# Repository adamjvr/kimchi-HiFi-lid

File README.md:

# Kimchi HiFi Lid — SGTL PCB

This directory contains the KiCad hardware files for the **SGTL5000-based audio PCB variant** of the Kimchi HiFi Lid project.

The board is an audio codec / interface PCB intended to mate with the main Kimchi hardware through high-density board-to-board connectors. It includes the audio codec, clocking, analog I/O connectors, EEPROM, local power filtering, and supporting passives required for the SGTL audio path.

## Design overview

Primary design intent:

- Provide a compact audio codec board for the Kimchi HiFi Lid assembly.
- Interface the audio codec and related signals to the parent system through two 60-pin Hirose board-to-board connectors.
- Break out analog audio through RCA and 3.5 mm audio connectors.
- Provide local clocking, EEPROM, level/interface support, and power filtering around the codec.

## Main functional blocks

- **Audio codec:** `U2` — `SGTL5000XNLA3`, NXP SGTL5000 stereo audio codec.
- **Clock source:** `X1` — `ASFL1-12.288MHZ-EC-T`, 12.288 MHz oscillator.
- **EEPROM:** `U1` — `24C32` / `M24C32-FMC6TG` I²C EEPROM.
- **Board-to-board connectors:** `J2`, `J3` — `DF40HC(3.5)-60DS` 60-pin connectors.
- **Analog audio I/O:**
  - `J1`, `J4` — `RCJ-2123` RCA jacks.
  - `J5` — `54-00176` 3.5 mm audio jack.
  - `MIC_IN` and `MIC_BIAS` nets for microphone input support.
- **Logic support:** `U3` — `SN74LV1T34DBVRG4` single-bit buffer / level interface.
- **Power rails and filtering:** `VDD_5V`, `VDD_3V3`, `VDD_1V8`, ferrite beads, bulk capacitance, and local bypassing.

## Directory contents

| Path | Purpose |
|---|---|
| `kimchi_ulid.sch` | Main KiCad / Eeschema schematic. |
| `kimchi_ulid.sch-bak` | Backup copy of the schematic. |
| `kimchi_ulid.lib` | Local symbol library. |
| `kimchi_ulid-cache.lib` | Cached schematic symbols. |
| `kimchi_ulid.dcm` | KiCad symbol documentation metadata. |
| `kimchi_ulid.csv` | BOM / component export. See warning below before ordering. |
| `kimchi_ulid.xml` | KiCad-generated netlist / BOM source export. |
| `kimchi_ulid.pretty/` | Local KiCad footprints and related 3D assets. |
| `gerber/` | Exported manufacturing files. |
| `sym-lib-table` | KiCad symbol library table. |
| `fp-lib-table` | KiCad footprint library table. |

## KiCad version notes

This project uses the older KiCad / Eeschema file format, with the schematic stored as `kimchi_ulid.sch`.

For editing in a newer KiCad release:

1. Open the project/schematic in KiCad.
2. Let KiCad convert legacy schematic/library data if prompted.
3. Save the converted project on a new branch before overwriting the original files.
4. Re-run ERC, DRC, BOM export, and Gerber generation after conversion.

## Fabrication notes

The `gerber/` directory contains exported fabrication data, including copper, solder mask, silkscreen, fabrication, and edge-cut files.

Before sending this board out for manufacture, regenerate the manufacturing package from the current KiCad project and verify:

- Board outline and mounting holes.
- Layer stackup, especially the inner copper layers.
- DF40 connector orientation, stack height, and mating-board alignment.
- RCA and 3.5 mm jack mechanical clearance.
- Power rail assignments from the parent board.
- Audio routing, grounding, and codec analog supply filtering.
- I²C / digital audio signal mapping to the parent processor.

## Important BOM warning

The schematic in this SGTL folder uses `SGTL5000XNLA3` for `U2`, but the checked-in `kimchi_ulid.csv` may be stale and may still list `U2` as `WM8750CJLGEFL` from an earlier codec revision.

Do **not** order directly from the CSV without regenerating the BOM from the current schematic.

Recommended release process:

1. Open the schematic in KiCad.
2. Confirm `U2` is the intended SGTL5000 part.
3. Regenerate the BOM / CSV from the active schematic.
4. Compare the regenerated BOM against the committed `kimchi_ulid.csv`.
5. Update the CSV before fabrication or assembly.

## Bring-up checklist

Suggested first-power and validation flow:

- Inspect the board for solder bridges, especially around the codec QFN and DF40 connectors.
- Verify no shorts on `VDD_5V`, `VDD_3V3`, `VDD_1V8`, and ground before power-up.
- Power the board from a current-limited bench supply or through the intended parent board with current monitoring.
- Confirm local rails are present and stable.
- Confirm the 12.288 MHz oscillator output.
- Verify I²C communication with the codec and EEPROM.
- Confirm codec reset / enable behavior if controlled by the parent system.
- Test analog output at low level first, then validate full-scale playback.
- Test microphone input and bias only after confirming the audio codec is enumerating/configuring correctly.

## Status

Hardware design files and generated manufacturing outputs are present, but this directory should be treated as an engineering design package rather than a guaranteed production release. Regenerate and review all release outputs before ordering boards or parts.

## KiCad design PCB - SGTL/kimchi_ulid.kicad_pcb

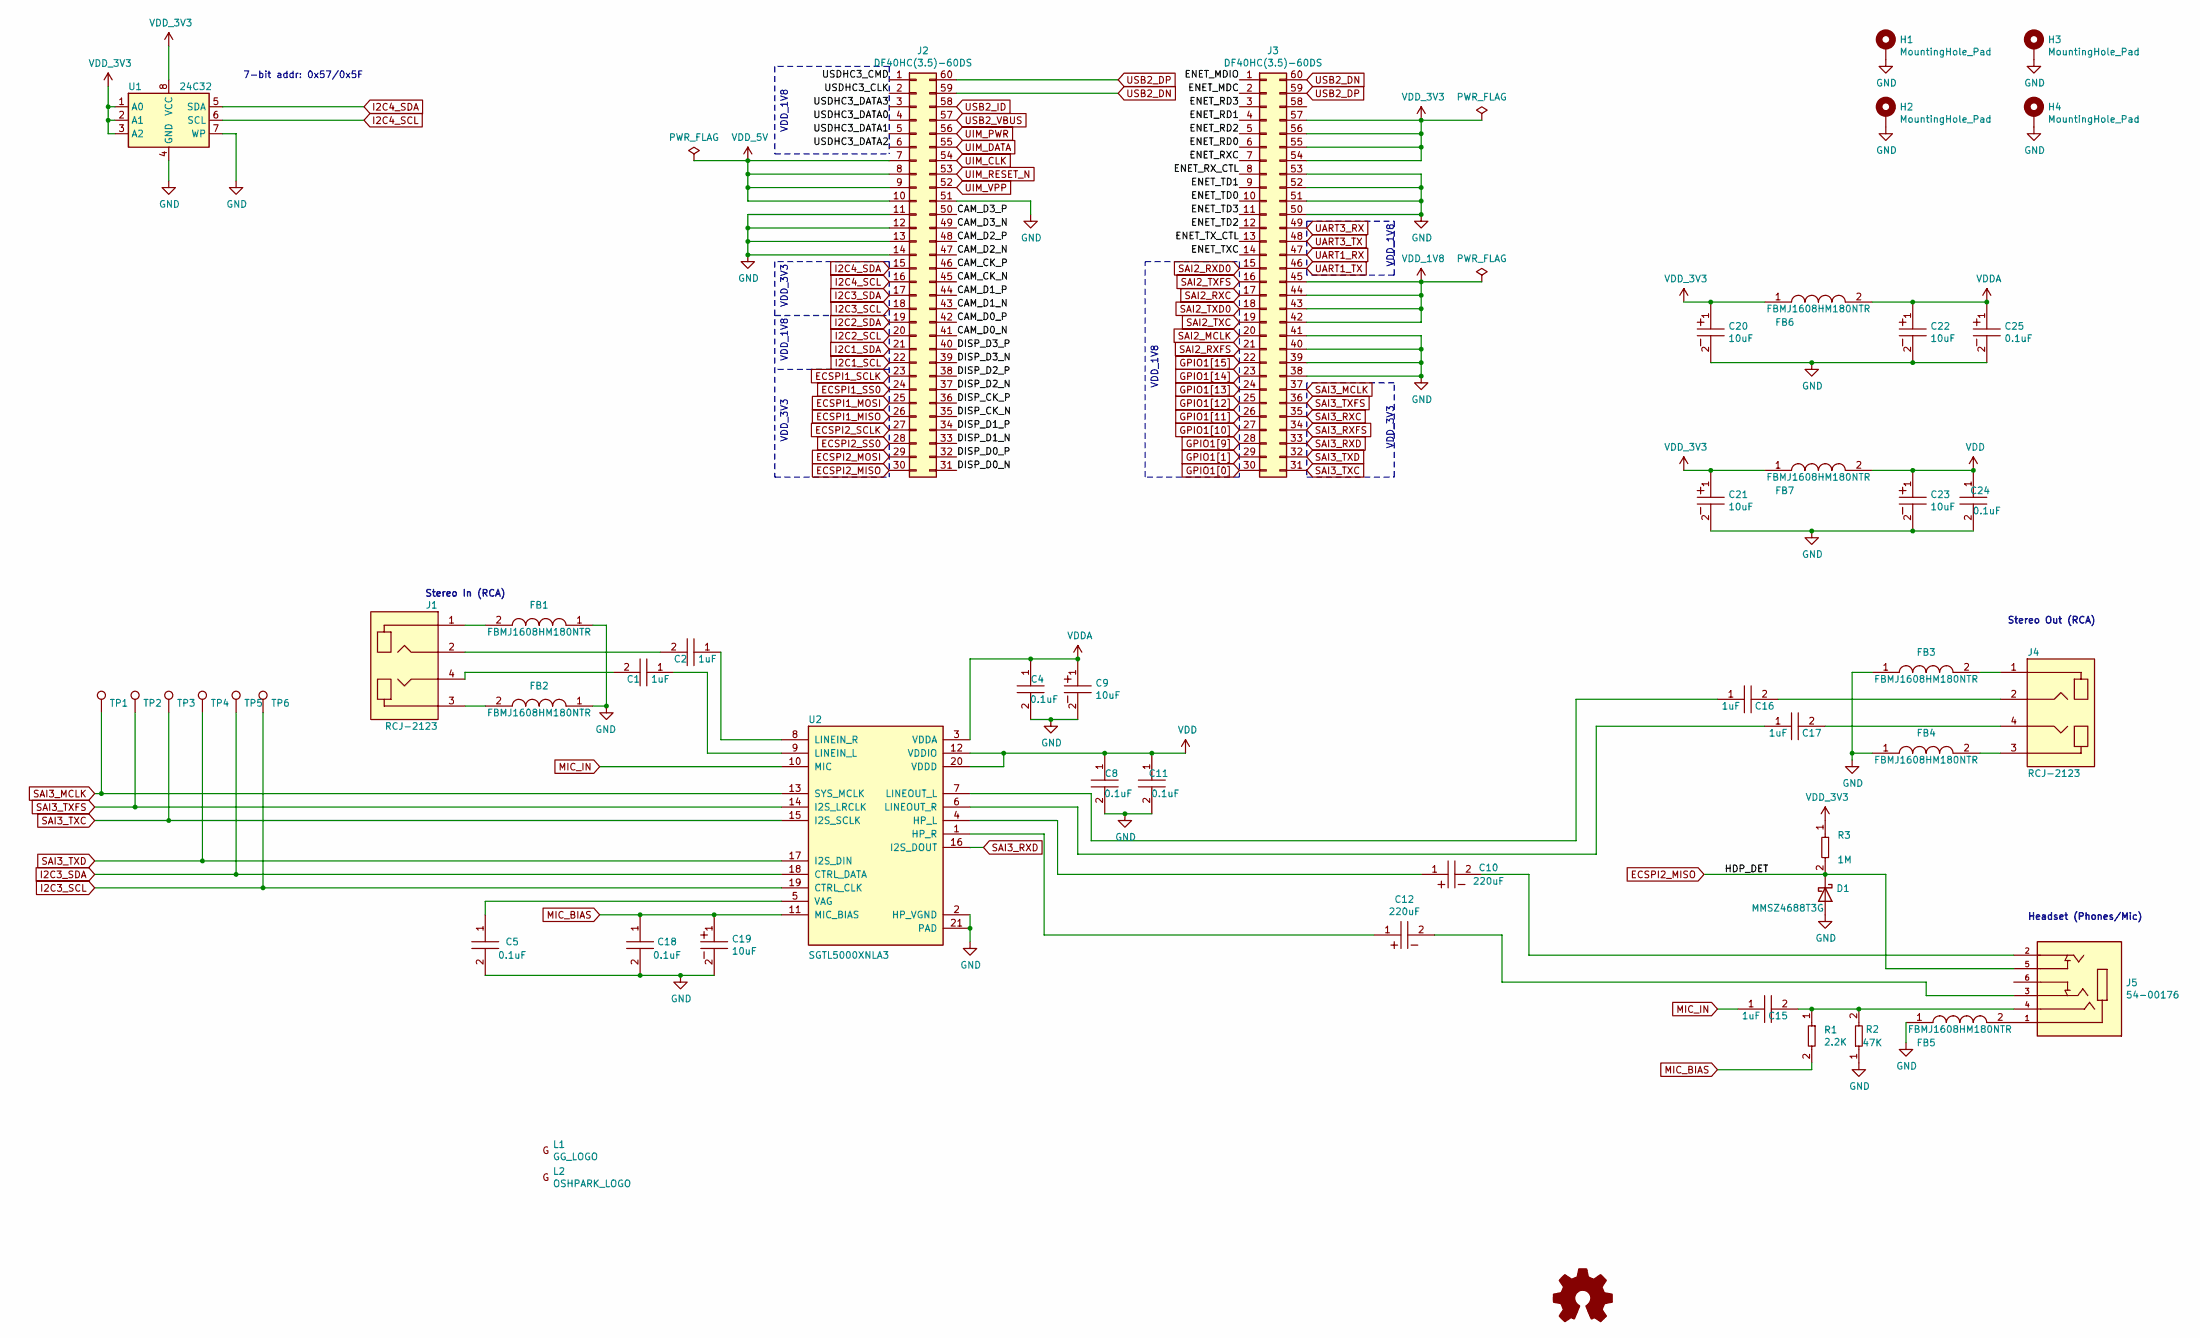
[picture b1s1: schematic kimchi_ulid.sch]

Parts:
C1, C2, C15, C16, C17: T491A105K010AT; C1206; Tolerance 10%; Voltage 10V; MFR# T491A105K010AT
C4, C5, C8, C11, C18, C24: C0402C104K9PACTU; C0402; Tolerance 10%; Voltage 6.3V; MFR# C0402C104K9PACTU
C9, C19, C20, C21, C22, C23: T494A106M006AT; Tolerance 20%; Voltage 6.3V; MFR# T494A106M006AT
C10, C12: T491D227M010AT; Tolerance 10%; Voltage 10VDC; MFR# T491D227M010AT
C25: UZP1H0R1MCL1GB; Tolerance 20%; Voltage 50V; MFR# UZP1H0R1MCL1GB
D1: MMSZ4688T3G
FB1, FB2, FB3, FB4, FB5, FB6, FB7: FBMJ1608HM180NTR; R0603; Tolerance *; Voltage *; MFR# FBMJ1608HM180NTR
H1, H2, H3, H4: MountingHole_Pad; MountingHole_3mm_Pad
J1, J4: RCJ-2123; Tolerance *; Voltage 24VDC; MFR# RCJ-2123
J2, J3: DF40HC(3.5)-60DS
J5: 54-00176; Tolerance *; Voltage *; MFR# 54-00176
L1: GG_LOGO; groupgets_logo
L2: OSHPARK_LOGO; oshpark_logo
LOGO1: Logo_Open_Hardware_Small; OSHW-Logo_5.7x6mm_SilkScreen
R1: RC0402JR-072K2L; R0402; Tolerance 1%; Voltage *; MFR# RC0402JR-072K2L
R2: RC0603FR-0747KL; R0603; Tolerance 1%; Voltage *; MFR# RC0603FR-0747KL
R3: AC0402FR-071ML; R0402; Tolerance 1%; Voltage *; MFR# AC0402FR-071ML
TP1, TP2, TP3, TP4, TP5, TP6: TestPoint; TestPoint_Pad_D1.0mm
U1: 24C32; DFN-8-1EP_3x2mm_P0.5mm_EP1.36x1.46mm; Part M24C32-FMC6TG
U2: SGTL5000XNLA3; QFN40P300X300X60-21N; Tolerance *; Voltage 3.3V; MFR# SGTL5000XNLA3

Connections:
/CAM_CK_N: J2.45
/CAM_CK_P: J2.46
/CAM_D0_N: J2.41
/CAM_D0_P: J2.42
/CAM_D1_N: J2.43
/CAM_D1_P: J2.44
/CAM_D2_N: J2.47
/CAM_D2_P: J2.48
/CAM_D3_N: J2.49
/CAM_D3_P: J2.50
/DISP_CK_N: J2.35
/DISP_CK_P: J2.36
/DISP_D0_N: J2.31
/DISP_D0_P: J2.32
/DISP_D1_N: J2.33
/DISP_D1_P: J2.34
/DISP_D2_N: J2.37
/DISP_D2_P: J2.38
/DISP_D3_N: J2.39
/DISP_D3_P: J2.40
/ENET_MDC: J3.2
/ENET_MDIO: J3.1
/ENET_RD0: J3.6
/ENET_RD1: J3.4
/ENET_RD2: J3.5
/ENET_RD3: J3.3
/ENET_RXC: J3.7
/ENET_RX_CTL: J3.8
/ENET_TD0: J3.10
/ENET_TD1: J3.9
/ENET_TD2: J3.12
/ENET_TD3: J3.11
/ENET_TXC: J3.14
/ENET_TX_CTL: J3.13
/USDHC3_CLK: J2.2
/USDHC3_CMD: J2.1
/USDHC3_DATA0: J2.4
/USDHC3_DATA1: J2.5
/USDHC3_DATA2: J2.6
/USDHC3_DATA3: J2.3
ECSPI1_MISO: J2.26
ECSPI1_MOSI: J2.25
ECSPI1_SCLK: J2.23
ECSPI1_SS0: J2.24
ECSPI2_MISO: D1.1 (K), J2.30, J5.5, R3.2
ECSPI2_MOSI: J2.29
ECSPI2_SCLK: J2.27
ECSPI2_SS0: J2.28
GND: C4.2, C5.2, C8.2, C9.2, C11.2, C18.2, C19.2, C20.2, C21.2, C22.2, C23.2, C24.2, C25.2, D1.2 (A), FB1.1, FB2.1, FB3.1, FB4.1, FB5.1, H1.1, H2.1, H3.1, H4.1, J2.11, J2.12, J2.13, J2.14, J2.51, J3.38, J3.39, J3.40, J3.41, J3.50, J3.51, J3.52, J3.53, R2.1, U1.4 (GND), U1.7 (WP), U2.2 (HP_VGND), U2.21 (PAD)
GPIO1[0]: J3.30
GPIO1[1]: J3.29
GPIO1[9]: J3.28
GPIO1[10]: J3.27
GPIO1[11]: J3.26
GPIO1[12]: J3.25
GPIO1[13]: J3.24
GPIO1[14]: J3.23
GPIO1[15]: J3.22
I2C1_SCL: J2.22
I2C1_SDA: J2.21
I2C2_SCL: J2.20
I2C2_SDA: J2.19
I2C3_SCL: J2.18, TP6.1, U2.19 (CTRL_CLK)
I2C3_SDA: J2.17, TP5.1, U2.18 (CTRL_DATA)
I2C4_SCL: J2.16, U1.6 (SCL)
I2C4_SDA: J2.15, U1.5 (SDA)
MIC_BIAS: C18.1, C19.1, R1.2, U2.11 (MIC_BIAS)
MIC_IN: C15.1, U2.10 (MIC)
unnamed: C1.1, U2.9 (LINEIN_L)
unnamed: C1.2, J1.4
unnamed: C2.1, U2.8 (LINEIN_R)
unnamed: C2.2, J1.2
unnamed: C5.1, U2.5 (VAG)
unnamed: C10.1, U2.4 (HP_L)
unnamed: C10.2, J5.2
unnamed: C12.1, U2.1 (HP_R)
unnamed: C12.2, J5.3
unnamed: C15.2, J5.4, R1.1, R2.2
unnamed: C16.2, J4.2
unnamed: C17.2, J4.4
unnamed: FB1.2, J1.1
unnamed: FB2.2, J1.3
unnamed: FB3.2, J4.1
unnamed: FB4.2, J4.3
unnamed: FB5.2, J5.1
SAI2_MCLK: J3.20
SAI2_RXC: J3.17
SAI2_RXD0: J3.15
SAI2_RXFS: J3.21
SAI2_TXC: J3.19
SAI2_TXD0: J3.18
SAI2_TXFS: J3.16
SAI3_MCLK: J3.37, TP1.1, U2.13 (SYS_MCLK)
SAI3_RXC: J3.35
SAI3_RXD: J3.33, U2.16 (I2S_DOUT)
SAI3_RXFS: J3.34
SAI3_TXC: J3.31, TP3.1, U2.15 (I2S_SCLK)
SAI3_TXD: J3.32, TP4.1, U2.17 (I2S_DIN)
SAI3_TXFS: J3.36, TP2.1, U2.14 (I2S_LRCLK)
UART1_RX: J3.47
UART1_TX: J3.46
UART3_RX: J3.49
UART3_TX: J3.48
UIM_CLK: J2.54
UIM_DATA: J2.55
UIM_PWR: J2.56
UIM_RESET_N: J2.53
UIM_VPP: J2.52
USB2_DN: J2.59, J3.60
USB2_DP: J2.60, J3.59
USB2_ID: J2.58
USB2_VBUS: J2.57
VDD: C8.1, C11.1, C23.1, C24.1, FB7.2, U2.12 (VDDIO), U2.20 (VDDD)
VDDA: C4.1, C9.1, C22.1, C25.1, FB6.2, U2.3 (VDDA)
VDD_1V8: J3.42, J3.43, J3.44, J3.45
VDD_3V3: C20.1, C21.1, FB6.1, FB7.1, J3.54, J3.55, J3.56, J3.57, R3.1, U1.1 (A0), U1.2 (A1), U1.3 (A2), U1.8 (VCC)
VDD_5V: J2.7, J2.8, J2.9, J2.10

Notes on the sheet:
7-bit addr: 0x57/0x5F
VDD_1V8
VDD_3V3
Headset (Phones/Mic)
Stereo Out (RCA)
Stereo In (RCA)

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
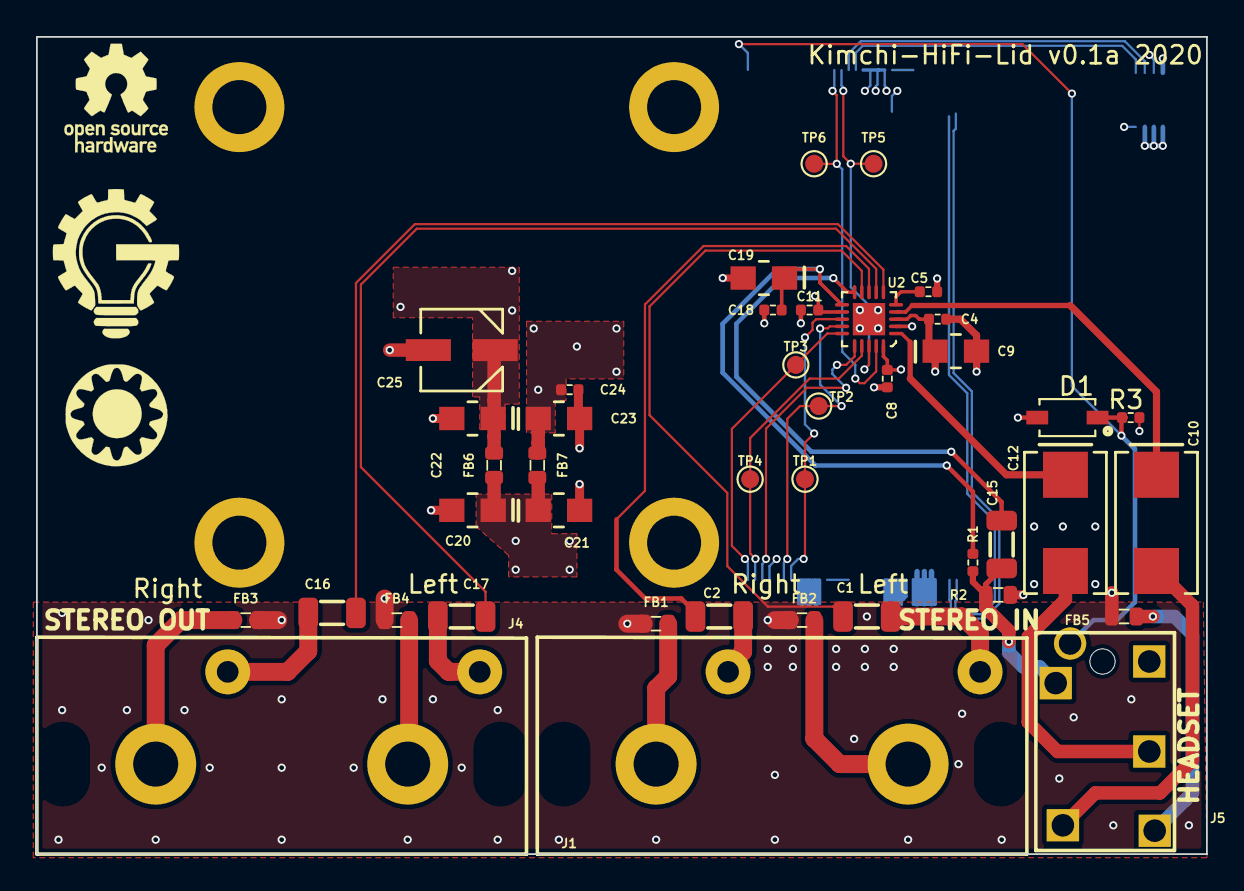
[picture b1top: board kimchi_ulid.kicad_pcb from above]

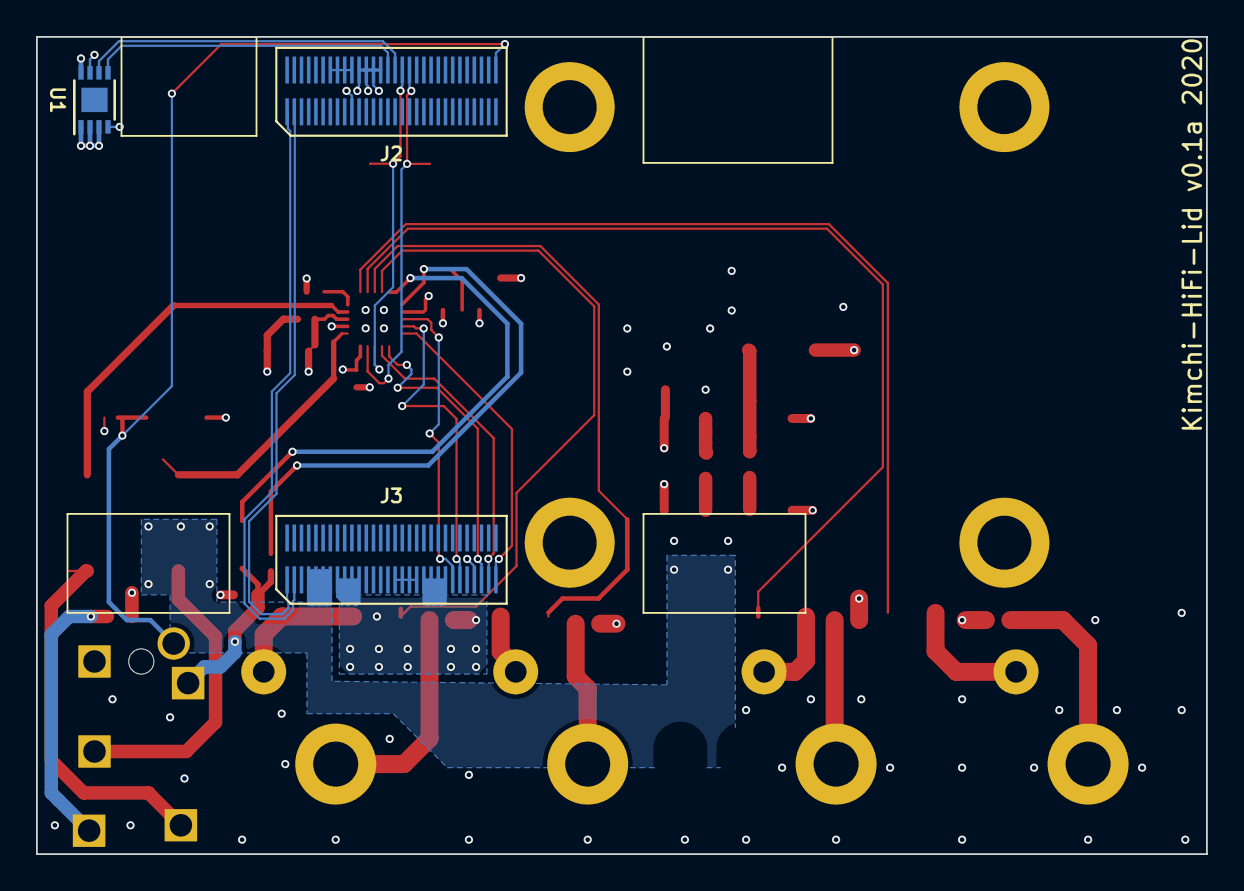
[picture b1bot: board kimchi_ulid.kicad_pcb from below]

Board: 4 copper layers, 65.0 x 45.4 mm, 51 parts (3 on the bottom side), 39 nets.

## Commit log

2020-12-16 Progress
    Board layout and shape defined, schematic in the process of rework, changing over to Wolfson DAC.
2020-12-16 redesigned circuit around WM8750 codec, added needed components to library
2020-12-17 Route In Progress
    Now doing the intial route of the board, still very much a work in progress, have the pwoer planes figured out and general component placenment. All components now have 3D models.
2020-12-23 First Route Pass Completed
    Completed first pass of routting the board. Need to adjust trace width for analog front ends for audio in and out.
2020-12-23 MCLK Jumper
    MCLK jumper added, trace width tweaked and DRC passed.
2020-12-29 MCLK Traces
    MCLK trace moved
2021-01-05 PCB tweaks
    fixed crooked board edge. Corrected board dimension labels. Moved board inside project so that bottom left corner is the origin.
2021-01-31 Fab FIles
    Fab files generated
2021-06-01 SGTL Version
    New version of lid with new codec from NXP, PCB is almost done, need to check scheamtic with mwelling before finalizing route.
2021-06-02 SGTL Version
    SGTL version finished, need feedback, chip is weird the route is too
2021-06-04 Test Points
    Test points added, also traces cleaned up and widened in places where more current capacity is required or appreciated.
2021-06-15 Headphone Detect and DRC
    Cleared DRC violations, added and implemented a headphone detect circuit.
2021-06-16 Channel Swap
    Swapped right and left channels on input, they were backwards. Changed soldermask rules so fab can make their own.
2026-06-16 Revise README for Kimchi HiFi Lid project
    Updated README to reflect new project details and design overview for the SGTL5000-based audio PCB variant.

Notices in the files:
parts and their libraries:
Copyright 2016 Accelerated Designs. All rights reserved.
